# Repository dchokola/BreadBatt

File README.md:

# BreadBatt

## What's New in Revision 1
* 100 mils longer profile to let USB overhang the breadboard if needed
* extra pins prevent misalignment
* +5 V USB output pin
* fancy new logo and layout optimized for clear silkscreen on black FR4
* 100% of parts on PCBA now have 3D models
## Features
* uses a single, cheap, easy-to-source 16340 lithium-ion battery
* supplies 3.3 V at up to 2 A
* on/off switch
* on/off and charging LEDs
* built-in thermal and short-circuit protection
* microUSB for charging
* auxilliary +5 V input for charging
* USB +5 V available to breadboard while connected
* silkscreened labels on pins
* open source design with bill of materials

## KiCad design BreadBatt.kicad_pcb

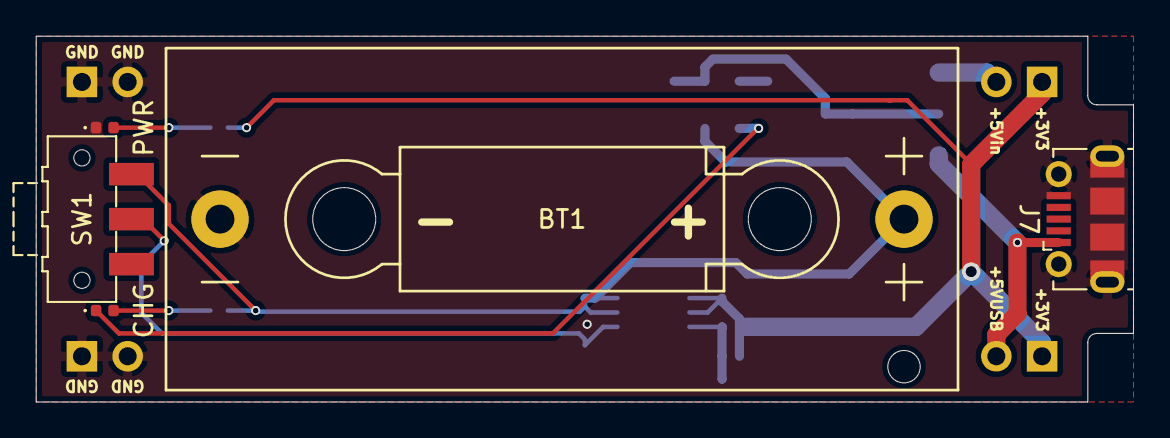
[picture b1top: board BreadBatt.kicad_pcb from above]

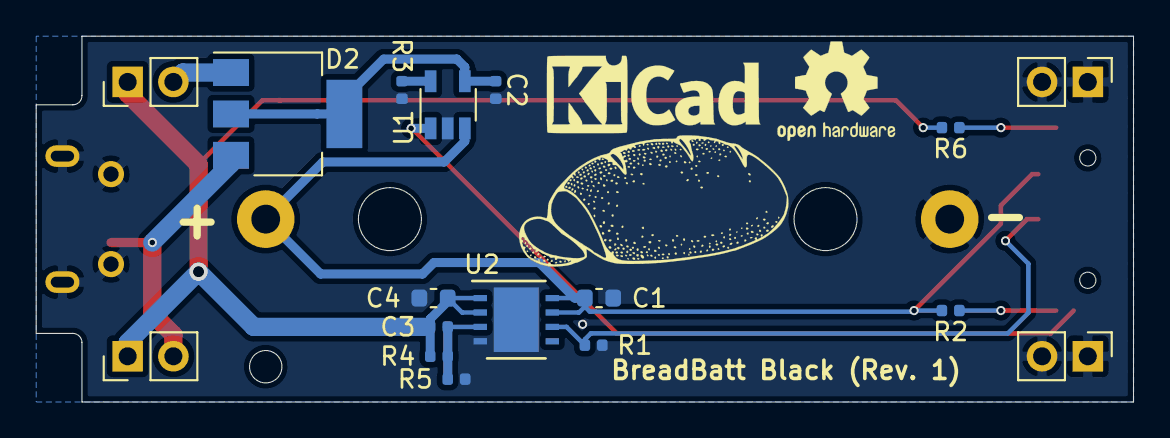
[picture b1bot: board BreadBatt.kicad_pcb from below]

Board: 2 copper layers, 61.0 x 20.3 mm, 22 parts (17 on the bottom side), 12 nets.

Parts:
BT1: 3.7 V Li-Ion 16340; BHC-CR123A
C1, C4: 10u; C_0603_1608Metric
C2: 1u; C_0402_1005Metric
C3: 470n; C_0402_1005Metric
D1: LED, Yellow; LED_0402_1005Metric
D2: BAT120C,115; SOT-223-3_TabPin2
D3: LED, Green; LED_0402_1005Metric
J1, J2, J3, J4: Conn_01x02; PinHeader_1x02_P2.54mm_Vertical
J7: Conn_01x05_Shielded; USB_Micro-B_Molex-105017-0001
R1: 100k; R_0402_1005Metric
R2, R5, R6: 1k; R_0402_1005Metric
R3: 1k27; R_0402_1005Metric
R4: 5k6; R_0402_1005Metric
SW1: SW_SPDT; SW_SPDT_CK-JS102011SAQN
U1: LTC4054ES5-4.2; TSOT-23-5
U2: LD39200D; DFN-8-1EP_4x4mm_P0.8mm_EP2.5x3.6mm

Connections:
+3V3: C3.1, C4.1, J1.1, J3.1, R4.2, R6.2, U2.1, U2.2
+5V: D2.1, J1.2
+BATT: BT1.1, C1.2, R2.2, SW1.1, U1.3, U2.7, U2.8
-BATT: BT1.2, C1.1, C2.1, C4.2, D3.1, J2.1, J2.2, J4.1, J4.2, J7.5, J7.SH, R1.1, R3.1, R5.1, U1.2, U2.4, U2.9
unnamed: C2.2, D2.2, U1.4
unnamed: C3.2, R4.1, R5.2, U2.3
unnamed: D1.1, U1.1
unnamed: D1.2, R2.1
unnamed: D3.2, R6.1
unnamed: R1.2, SW1.2, U2.6
unnamed: R3.2, U1.5
VBUS: D2.3, J3.2, J7.1

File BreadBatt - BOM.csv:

Reference, Value, Footprint, Datasheet, Manufacturer, Manufacturer Part Number, Vendor, Vendor Part Number
"U1","LTC4054ES5-4.2","Package_TO_SOT_SMD:TSOT-23-5","http://cds.linear.com/docs/en/datasheet/405442xf.pdf","Linear Technology/Analog Devices","LTC4054ES5-4.2#TRMPBF","Digi-Key","LTC4054ES5-4.2#TRMPBFCT-ND"
"J7","Conn_01x05_Shielded","Connector_USB:USB_Micro-B_Molex-105017-0001","~","Molex, LLC","1050170001","Digi-Key","WM1399CT-ND"
"D2","BAT120C,115","Package_TO_SOT_SMD:SOT-223-3_TabPin2","https://assets.nexperia.com/documents/data-sheet/BAT120_SERIES.pdf","Nexperia USA Inc.","BAT120C,115","Digi-Key","1727-5450-1-ND"
"BT1","3.7 V Li-Ion 16340","KiCad:BHC-CR123A","http://shogyo.com/wp-content/themes/shogyo/pdf/bhc-cr123a(re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","Shogyo International Corp.","BHC-CR123A","",""
"R3","1k27","Resistor_SMD:R_0402_1005Metric","~","Panasonic Electronic Components","ERJ-2RKF1271X","Digi-Key","P1.27KLCT-ND"
"C2","1u","Capacitor_SMD:C_0402_1005Metric","~","TDK Corporation","CGB2A1X5R1C105K033BC","Digi-Key","445-13181-1-ND"
"D3","LED, Green","LED_SMD:LED_0402_1005Metric","~","Wurth Electronics Inc.","150040VS73240","Digi-Key","732-11992-1-ND"
"D1","LED, Yellow","LED_SMD:LED_0402_1005Metric","~","Wurth Electronics Inc.","150040YS73240","Digi-Key","732-11993-1-ND"
"R6","1k","Resistor_SMD:R_0402_1005Metric","~","Samsung Electro-Mechanics","RC1005F102CS","Digi-Key","1276-3430-1-ND"
"R2","1k","Resistor_SMD:R_0402_1005Metric","~","Samsung Electro-Mechanics","RC1005F102CS","Digi-Key","1276-3430-1-ND"
"U2","LD39200D","Package_DFN_QFN:DFN-8-1EP_4x4mm_P0.8mm_EP2.5x3.6mm","https://www.st.com/content/ccc/resource/technical/document/d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","STMicroelectronics","LD39200DPUR","Digi-Key","497-14961-1-ND"
"R5","1k","Resistor_SMD:R_0402_1005Metric","~","Samsung Electro-Mechanics","RC1005F102CS","Digi-Key","1276-3430-1-ND"
"R4","5k6","Resistor_SMD:R_0402_1005Metric","~","Yageo","RC0402JR-075K6L","Digi-Key","311-5.6KJRCT-ND"
"C1","10u","Capacitor_SMD:C_0603_1608Metric","~","Samsung Electro-Mechanics","CL10X106MQ8NNNC","Digi-Key","1276-6827-1-ND"
"C3","470n","Capacitor_SMD:C_0402_1005Metric","~","Samsung Electro-Mechanics","CL05F474ZQ5NNNC","Digi-Key","1276-1752-1-ND"
"C4","10u","Capacitor_SMD:C_0603_1608Metric","~","Samsung Electro-Mechanics","CL10X106MQ8NNNC","Digi-Key","1276-6827-1-ND"
"R1","100k","Resistor_SMD:R_0402_1005Metric","~","Samsung Electro-Mechanics","RC1005F103CS","Digi-Key","1276-3431-1-ND"
"J3","+3V3","TestPoint:TestPoint_THTPad_2.0x2.0mm_Drill1.0mm","~"
"J5","+3V3","TestPoint:TestPoint_THTPad_2.0x2.0mm_Drill1.0mm","~"
"J4","GND","TestPoint:TestPoint_THTPad_D2.0mm_Drill1.0mm","~"
"J6","GND","TestPoint:TestPoint_THTPad_D2.0mm_Drill1.0mm","~"
"J1","+5Vin","TestPoint:TestPoint_THTPad_2.0x2.0mm_Drill1.0mm","~"
"J2","GND","TestPoint:TestPoint_THTPad_D2.0mm_Drill1.0mm","~"
"SW1","SW_SPDT","Button_Switch_SMD:SW_SPDT_CK-JS102011SAQ","https://www.ckswitches.com/media/1422/js.pdf","C&K","JS102011SAQN","Digi-Key","401-1999-1-ND"

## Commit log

2020-06-20 BreadBatt Revision 0
2020-06-20 BreadBatt Revision 1
